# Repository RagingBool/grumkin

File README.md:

# Grumkin 0.5.0.0 [IN DEVELOPMENT]
Grumkin: A 6-channel PWM LED driver

## Links
* Git repository: https://github.com/RagingBool/grumkin

## License
Apache License 2.0 (http://www.apache.org/licenses/LICENSE-2.0)
Copyright 2015 Raging Bool (http://ragingbool.org)

## Release Notes
### Version 0.1

* **Version 0.5.0.0** [IN DEVELOPMENT]

* **Version 0.4.0.0** [2015-02-19]
  * Creating a PCB

* **Version 0.3.0.0** [2015-02-18]
  * Adding indicator LEDs

* **Version 0.2.0.0** [2015-02-18]
  * Adding a Fritzing prototype schematics

* **Version 0.1.0.0** [2015-02-17]
  * Drawing a basic Grumkin circuit

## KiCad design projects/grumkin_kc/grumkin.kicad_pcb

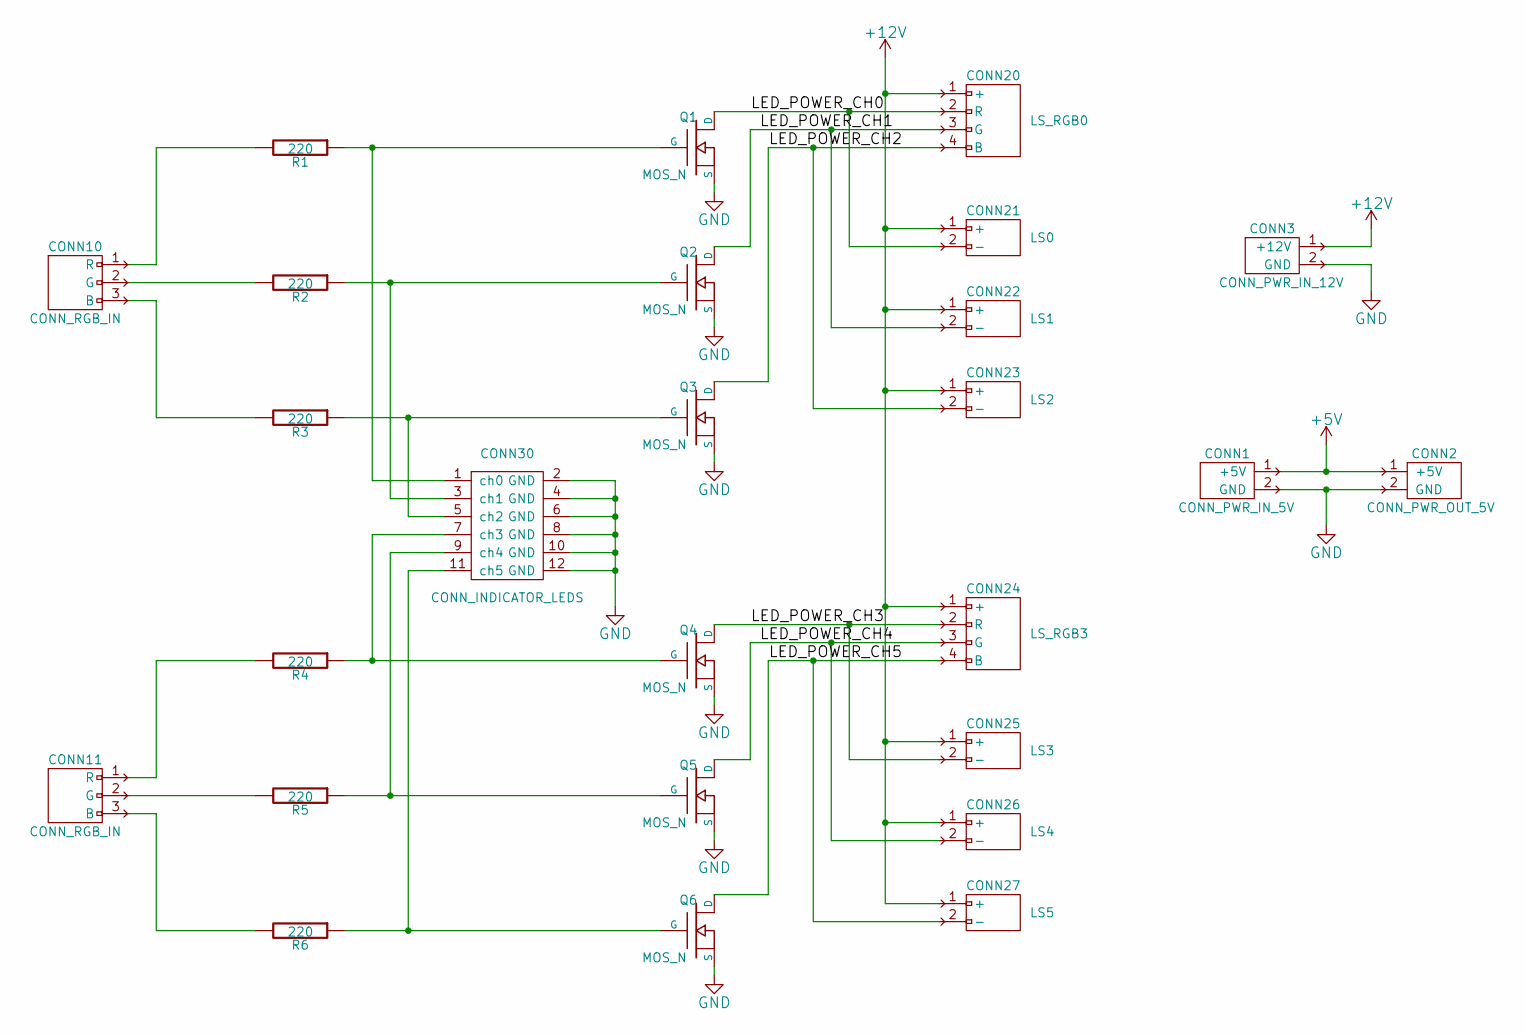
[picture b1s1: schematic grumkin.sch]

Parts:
CONN1: CONN_PWR_IN_5V; pin_strip_2
CONN2: CONN_PWR_OUT_5V; pin_strip_2
CONN3: CONN_PWR_IN_12V; pt_1,5-2-3,5-h
CONN10, CONN11: CONN_RGB_IN; pin_strip_3
CONN20: LS_RGB0; pt_1,5-4-3,5-h
CONN21: LS0; pt_1,5-2-3,5-h
CONN22: LS1; pt_1,5-2-3,5-h
CONN23: LS2; pt_1,5-2-3,5-h
CONN24: LS_RGB3; pt_1,5-4-3,5-h
CONN25: LS3; pt_1,5-2-3,5-h
CONN26: LS4; pt_1,5-2-3,5-h
CONN27: LS5; pt_1,5-2-3,5-h
CONN30: CONN_INDICATOR_LEDS; pin_strip_6x2
Q1, Q2, Q3, Q4, Q5, Q6: MOS_N; TO-220_FET-GDS_Vertical
R1, R2, R3, R4, R5, R6: 220; Resistor_Horizontal_RM15mm

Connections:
+5V: CONN1.1 (+5V), CONN2.1 (+5V)
+12V: CONN3.1 (+12V), CONN20.1 (+), CONN21.1 (+), CONN22.1 (+), CONN23.1 (+), CONN24.1 (+), CONN25.1 (+), CONN26.1 (+), CONN27.1 (+)
/LED_POWER_CH0: CONN20.2 (R), CONN21.2 (-), Q1.D
/LED_POWER_CH1: CONN20.3 (G), CONN22.2 (-), Q2.D
/LED_POWER_CH2: CONN20.4 (B), CONN23.2 (-), Q3.D
/LED_POWER_CH3: CONN24.2 (R), CONN25.2 (-), Q4.D
/LED_POWER_CH4: CONN24.3 (G), CONN26.2 (-), Q5.D
/LED_POWER_CH5: CONN24.4 (B), CONN27.2 (-), Q6.D
GND: CONN1.2 (GND), CONN2.2 (GND), CONN3.2 (GND), CONN30.2 (GND), CONN30.4 (GND), CONN30.6 (GND), CONN30.8 (GND), CONN30.10 (GND), CONN30.12 (GND), Q1.S, Q2.S, Q3.S, Q4.S, Q5.S, Q6.S
unnamed: CONN10.1 (R), R1.2
unnamed: CONN10.2 (G), R2.2
unnamed: CONN10.3 (B), R3.2
unnamed: CONN11.1 (R), R4.2
unnamed: CONN11.2 (G), R5.2
unnamed: CONN11.3 (B), R6.2
unnamed: CONN30.1 (ch0), Q1.G, R1.1
unnamed: CONN30.3 (ch1), Q2.G, R2.1
unnamed: CONN30.5 (ch2), Q3.G, R3.1
unnamed: CONN30.7 (ch3), Q4.G, R4.1
unnamed: CONN30.9 (ch4), Q5.G, R5.1
unnamed: CONN30.11 (ch5), Q6.G, R6.1

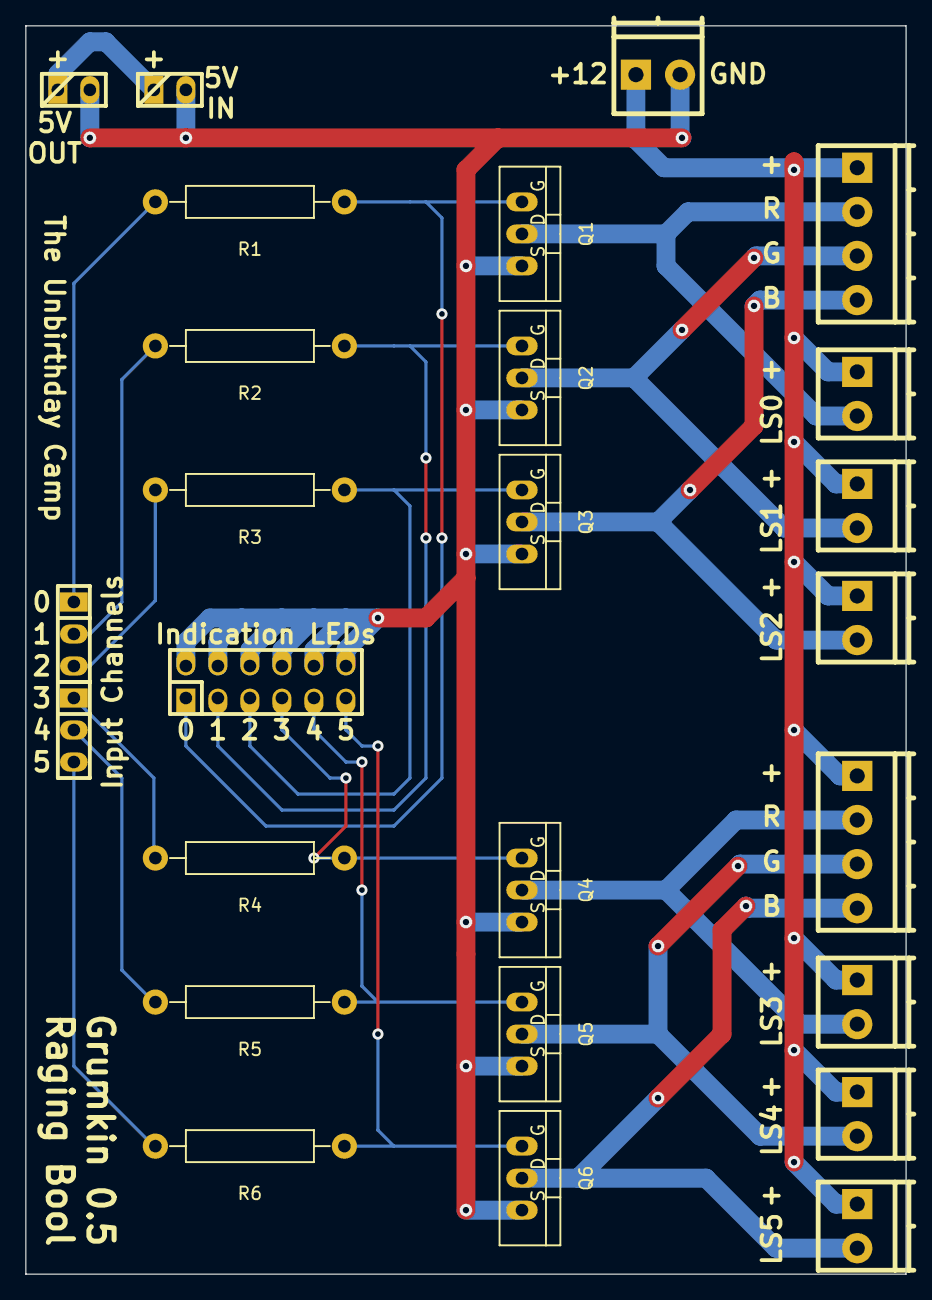
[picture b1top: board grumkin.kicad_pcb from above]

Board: 2 copper layers, 69.8 x 99.1 mm, 26 parts (0 on the bottom side), 21 nets.

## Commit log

2015-02-16 +comment
2015-02-16 Setting version to 0.0.0.0
2015-02-16 +README.md
2015-02-16 +empty KiCad project
2015-02-16 +empty schema
2015-02-16 Adding some metadata to schema
2015-02-16 ignoring *.bak files
2015-02-17 +grumkin.lib containing power input
2015-02-17 .gitignore: Ignorring bck files
2015-02-17 +grumkin.dcm
2015-02-17 Updating grumkin.pro
2015-02-17 Finishing the first version of the circuit
2015-02-17 Version: 0.0.0.0=>0.1.0.0
2015-02-17 Updating README.md
2015-02-17 Preparing for 0.1.0.0 release
2015-02-17 Version: 0.1.0.0=>0.2.0.0
2015-02-18 unignorring parts/
2015-02-18 +STP16NF06 N-Channel Power MOSFET.fzpz
2015-02-18 +grumkinPrototype.fzz
2015-02-18 Release notes
2015-02-18 Preparing for 0.2.0.0 release
2015-02-18 Version: 0.2.0.0=>0.3.0.0
2015-02-18 Adding indicator leds connector to schematics
2015-02-18 Adding indicator LEDs to Fritzing prototype
2015-02-18 Preparing for 0.3.0.0 release
2015-02-18 Version: 0.3.0.0=>0.4.0.0
2015-02-18 Annotating components
2015-02-18 Importing conn_pt-1,5 and pin_strip KiCad footprint libraries (including 3D models)
2015-02-18 +fp-lib-table
2015-02-18 Assigning footprints
2015-02-18 Generating grumkin.net
2015-02-18 Importing components into grumkin.kicad_pcb
2015-02-18 ignorring *.kicad_pcb-bak files
2015-02-18 Scheme: changing the transistor component
2015-02-18 Labeling LED_POWER lines
2015-02-18 Regenerating NET
2015-02-18 PCB: Arranging footprints
2015-02-19 grumkin.cmp: Updating timestamp
2015-02-19 Rewiring CONN_INDICATOR_LEDS
2015-02-19 Updating Indicator conector component and labeling LED power lines as such
2015-02-19 Regenerating grumkin.net
2015-02-19 Adding wires and texts to PCB
2015-02-19 PCB: Improving labels
2015-02-19 Preparing for 0.4.0.0 release
2015-02-19 Version: 0.4.0.0=>0.5.0.0
